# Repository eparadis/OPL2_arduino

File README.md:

### OPL2 and Arduino

Inspired by and based largely on [this project](https://hackaday.io/project/18995-opl2-audio-board-for-arduino-raspberry-pi).

This project glues a OPL2 FM synthesis chip by Yamaha to an Aduino Pro Mini. It was originally prototyped on a breadboard with an LCD and controls to allow parameters to be changed.

The goal is to make a eurorack compatible module that balances the flexibility
and simplicity inherent in a multi-voice 2-operator FM synthesis chip like the
YM3812 (OPL2). To this end, some parameters will be controlled by CV while
others will be menu-driven settings.

The prototype explored a variety of polyphonic "chord modes" as well as various
CV-to-operator-parameter mappings. This design should continue to allow that
exploration.

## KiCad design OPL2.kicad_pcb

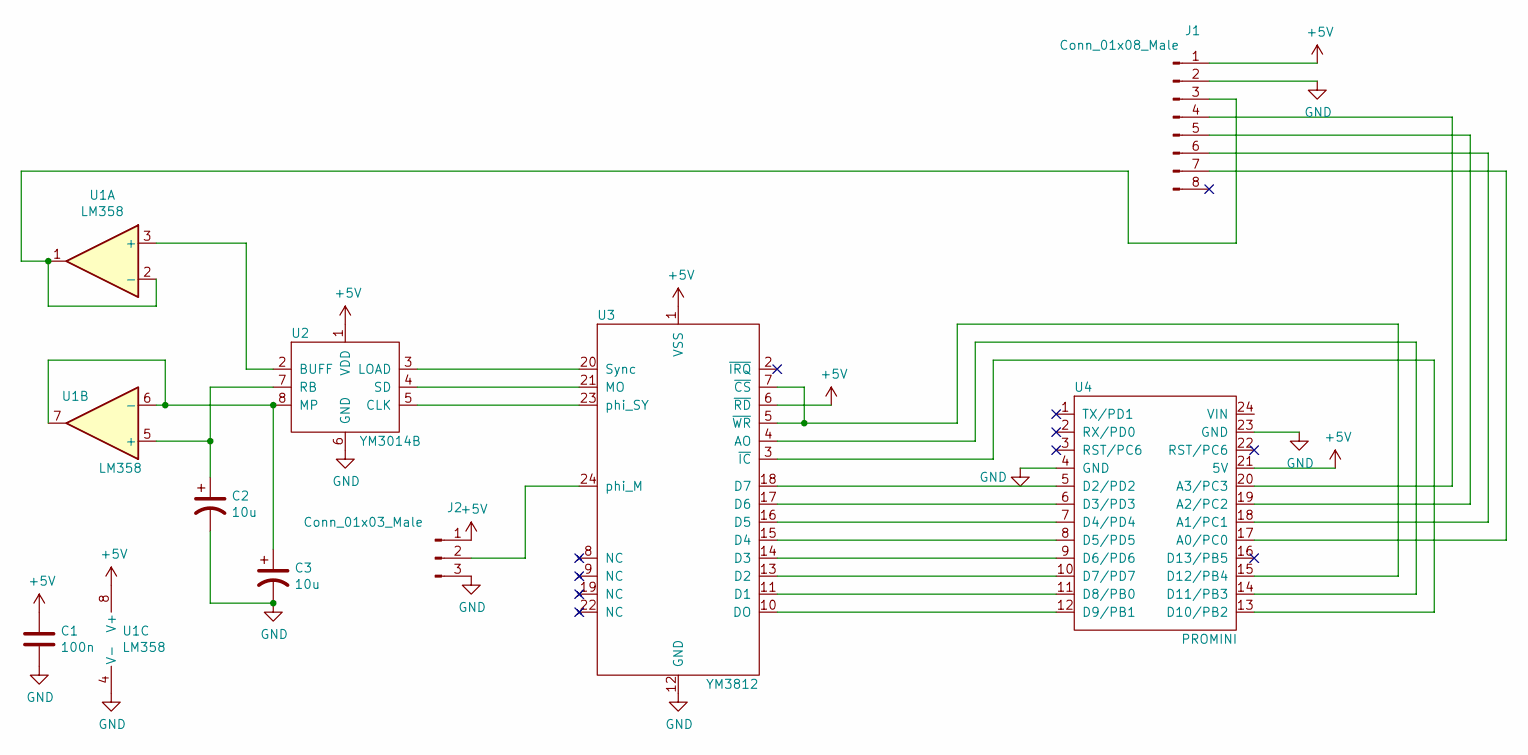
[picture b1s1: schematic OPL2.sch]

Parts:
C1: 100n; CP_Radial_D7.5mm_P2.50mm
C2, C3: 10u; CP_Radial_D7.5mm_P2.50mm
J1: Conn_01x08_Male; PinHeader_1x08_P2.54mm_Vertical
J2: Conn_01x03_Male; PinHeader_1x03_P2.54mm_Vertical
U1: LM358; DIP-8_W7.62mm_LongPads
U2: YM3014B; DIP-8_W7.62mm_LongPads
U3: YM3812; DIP-24_W15.24mm_LongPads
U4: PROMINI; DIP-24_W15.24mm_LongPads

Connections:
+5V: C1.1, J1.1, J2.1, U1.8 (V+), U2.1 (VDD), U3.1 (VSS), U3.6 (~RD), U4.21 (5V)
GND: C1.2, C2.2, C3.2, J1.2, J2.3, U1.4 (V-), U2.6 (GND), U3.12 (GND), U4.4 (GND), U4.23 (GND)
unnamed: C2.1, U1.5 (+), U2.7 (RB)
unnamed: C3.1, U1.6 (-), U1.7, U2.8 (MP)
unnamed: J1.3, U1.1, U1.2 (-)
unnamed: J1.4, U4.20 (A3/PC3)
unnamed: J1.5, U4.19 (A2/PC2)
unnamed: J1.6, U4.18 (A1/PC1)
unnamed: J1.7, U4.17 (A0/PC0)
unnamed: J2.2, U3.24 (phi_M)
unnamed: U1.3 (+), U2.2 (BUFF)
unnamed: U2.3 (LOAD), U3.20 (Sync)
unnamed: U2.4 (SD), U3.21 (MO)
unnamed: U2.5 (CLK), U3.23 (phi_SY)
unnamed: U3.3 (~IC), U4.13 (D10/PB2)
unnamed: U3.4 (AO), U4.14 (D11/PB3)
unnamed: U3.5 (~WR), U3.7 (~CS), U4.15 (D12/PB4)
unnamed: U3.10 (DO), U4.12 (D9/PB1)
unnamed: U3.11 (D1), U4.11 (D8/PB0)
unnamed: U3.13 (D2), U4.10 (D7/PD7)
unnamed: U3.14 (D3), U4.9 (D6/PD6)
unnamed: U3.15 (D4), U4.8 (D5/PD5)
unnamed: U3.16 (D5), U4.7 (D4/PD4)
unnamed: U3.17 (D6), U4.6 (D3/PD3)
unnamed: U3.18 (D7), U4.5 (D2/PD2)

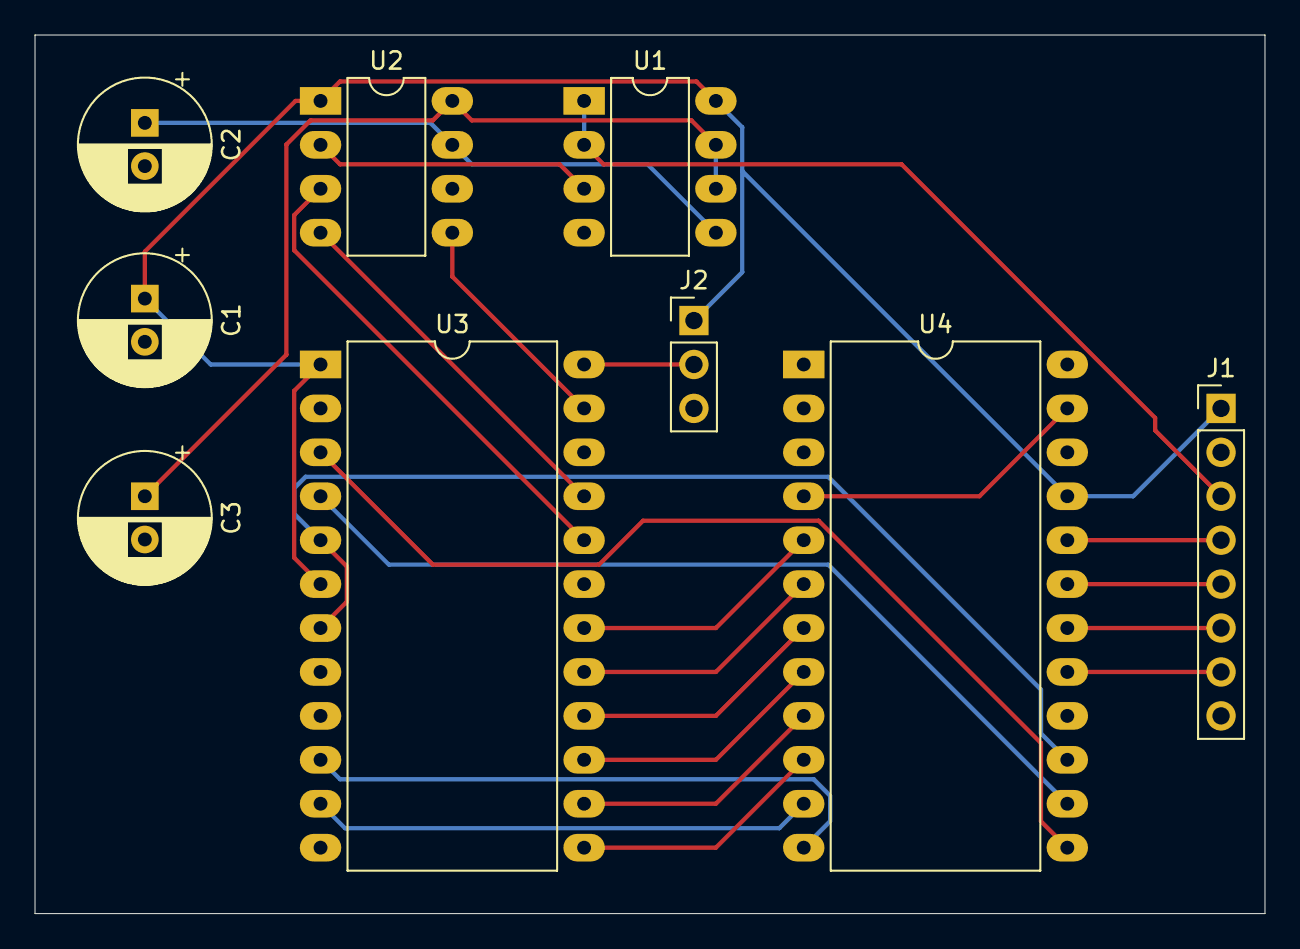
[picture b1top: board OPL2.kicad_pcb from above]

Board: 2 copper layers, 71.1 x 50.8 mm, 9 parts (0 on the bottom side), 25 nets.

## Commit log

2021-07-30 github kicad gitignore
2021-07-30 initial commit. everything but the clock generator
2021-07-30 add readme
2021-08-01 add footprints to everything; add header for clock subcircuit
